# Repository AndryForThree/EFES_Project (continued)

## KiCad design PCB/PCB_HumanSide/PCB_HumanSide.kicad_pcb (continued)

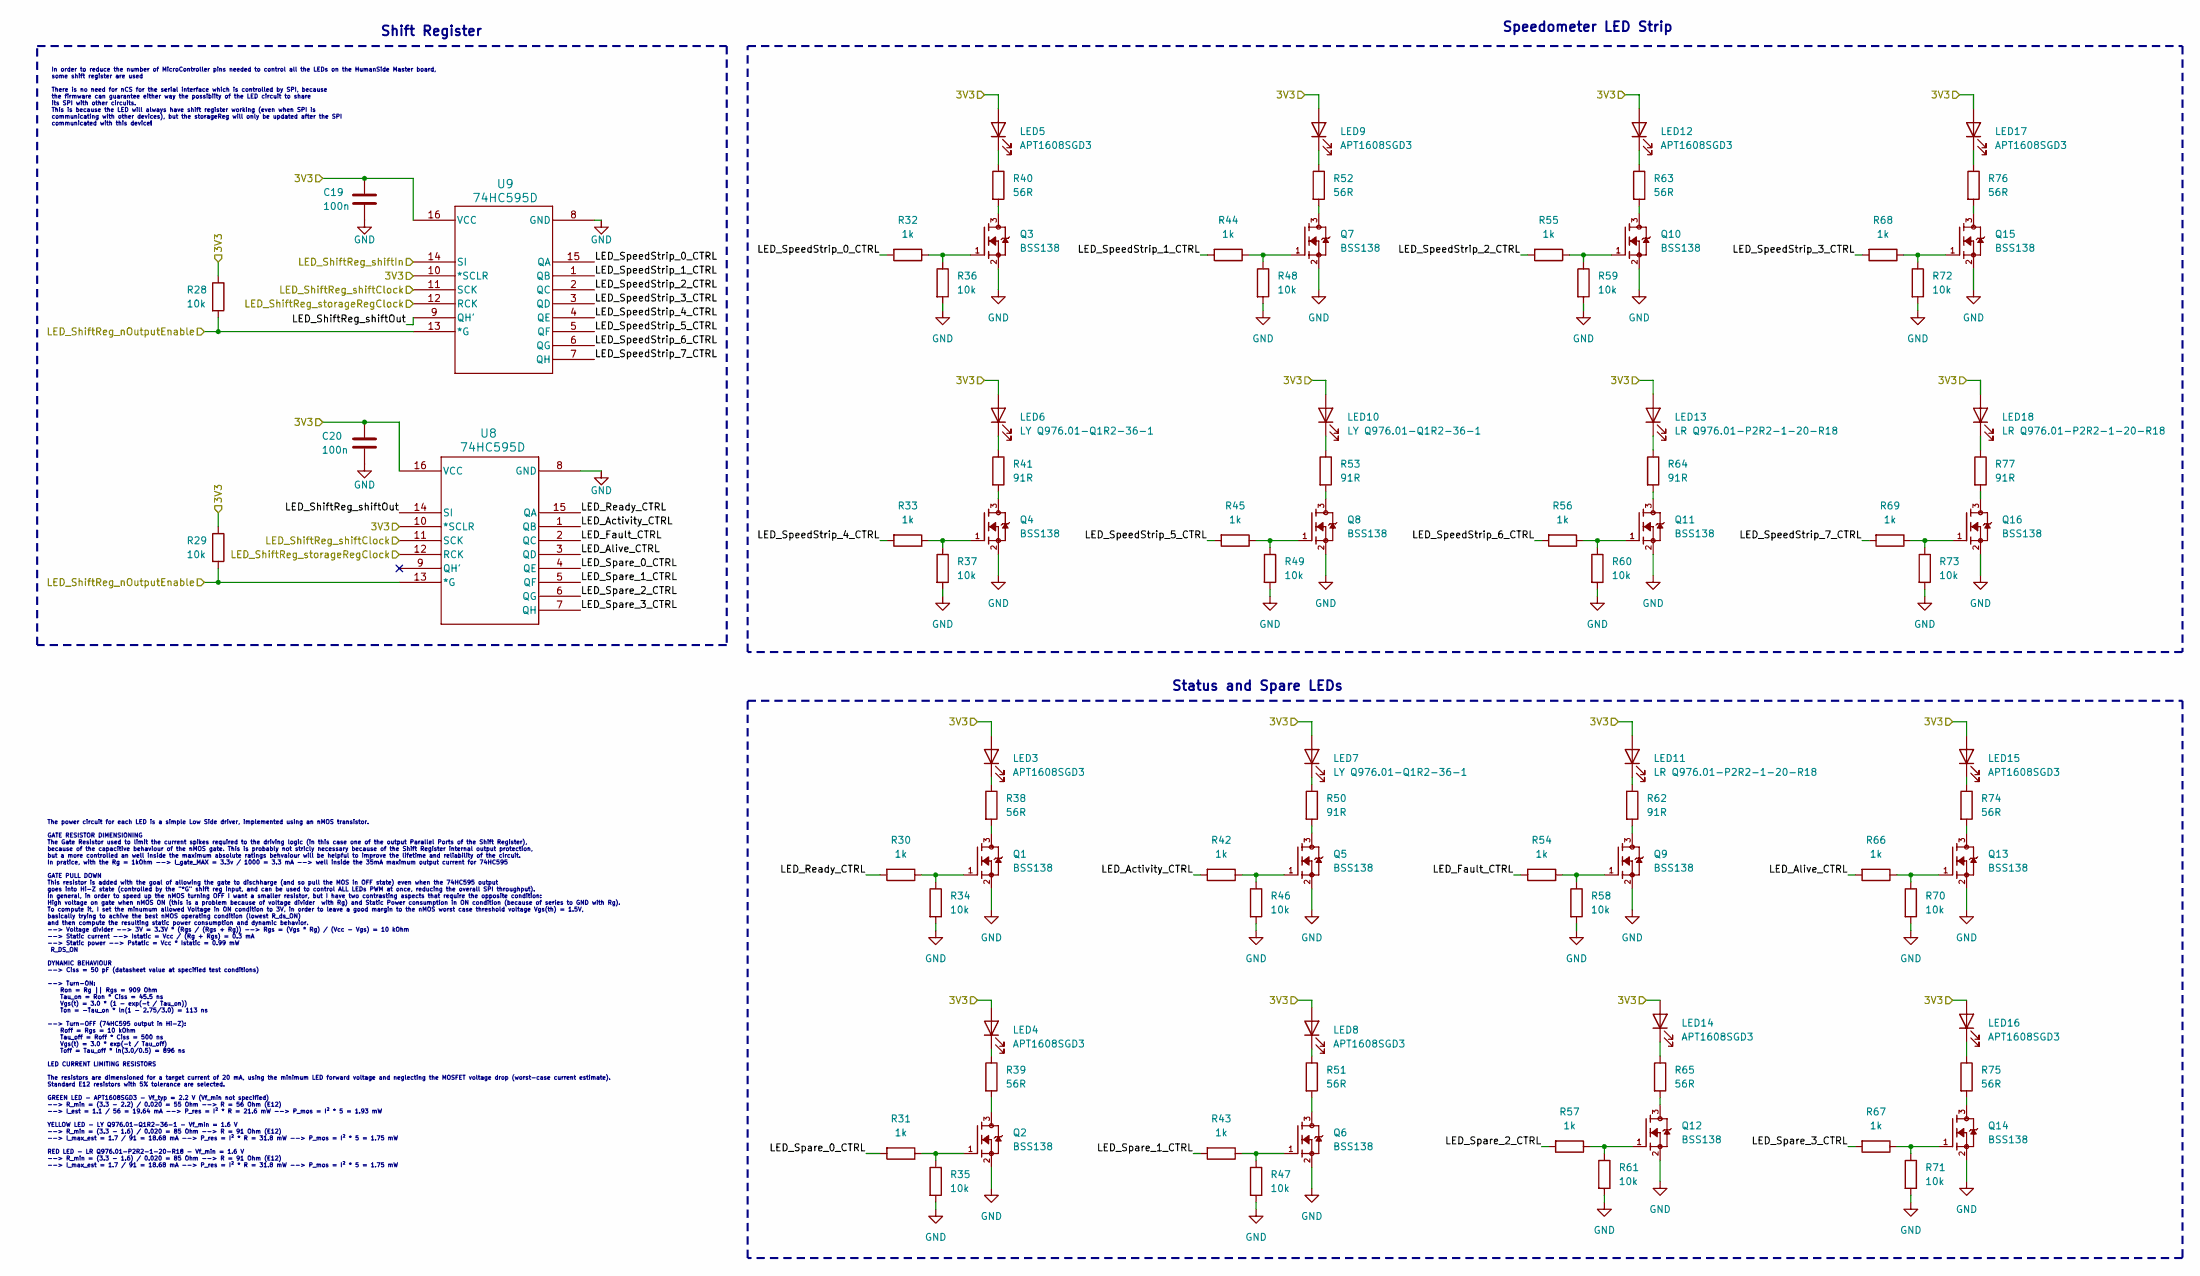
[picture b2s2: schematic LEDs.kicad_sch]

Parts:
C19, C20: 100n; C_0805_2012Metric_Pad1.18x1.45mm_HandSolder
LED3, LED4, LED5, LED8, LED9, LED12, LED14, LED15, LED16, LED17: APT1608SGD3; LED_0603_HandSolder
LED6, LED7, LED10: LY Q976.01-Q1R2-36-1; LED_0603_HandSolder
LED11, LED13, LED18: LR Q976.01-P2R2-1-20-R18; LED_0603_HandSolder
Q1, Q2, Q3, Q4, Q5, Q6, Q7, Q8, Q9, Q10, Q11, Q12, Q13, Q14, Q15, Q16: BSS138; SOT95P240X111-3N; MPN BSS138
R28, R29, R34, R35, R36, R37, R46, R47, R48, R49, R58, R59, R60, R61, R70, R71, R72, R73: 10k; R_0805_2012Metric_Pad1.20x1.40mm_HandSolder
R30, R31, R32, R33, R42, R43, R44, R45, R54, R55, R56, R57, R66, R67, R68, R69: 1k; R_0805_2012Metric_Pad1.20x1.40mm_HandSolder
R38, R39, R40, R51, R52, R63, R65, R74, R75, R76: 56R; R_0805_2012Metric_Pad1.20x1.40mm_HandSolder
R41, R50, R53, R62, R64, R77: 91R; R_0805_2012Metric_Pad1.20x1.40mm_HandSolder
U8, U9: 74HC595D; SOIC16_TOS-M

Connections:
/3V3: C19.2, C20.2, LED3.2 (A), LED4.2 (A), LED5.2 (A), LED6.2 (A), LED7.2 (A), LED8.2 (A), LED9.2 (A), LED10.2 (A), LED11.2 (A), LED12.2 (A), LED13.2 (A), LED14.2 (A), LED15.2 (A), LED16.2 (A), LED17.2 (A), LED18.2 (A), R28.1, R29.1, U8.10 (*SCLR), U8.16 (VCC), U9.10 (*SCLR), U9.16 (VCC); also elsewhere on the board
/LED_ShiftReg_nOutputEnable: R28.2, R29.2, U8.13 (*G), U9.13 (*G); also elsewhere on the board
/LED_ShiftReg_storageRegClock: U8.12 (RCK), U9.12 (RCK); also elsewhere on the board
/LEDs/LED_Activity_CTRL: R42.2, U8.1 (QB)
/LEDs/LED_Alive_CTRL: R66.2, U8.3 (QD)
/LEDs/LED_Fault_CTRL: R54.2, U8.2 (QC)
/LEDs/LED_Ready_CTRL: R30.2, U8.15 (QA)
/LEDs/LED_ShiftReg_shiftOut: U8.14 (SI), U9.9 (QH')
/LEDs/LED_Spare_0_CTRL: R31.2, U8.4 (QE)
/LEDs/LED_Spare_1_CTRL: R43.2, U8.5 (QF)
/LEDs/LED_Spare_2_CTRL: R57.2, U8.6 (QG)
/LEDs/LED_Spare_3_CTRL: R67.2, U8.7 (QH)
/LEDs/LED_SpeedStrip_0_CTRL: R32.2, U9.15 (QA)
/LEDs/LED_SpeedStrip_1_CTRL: R44.2, U9.1 (QB)
/LEDs/LED_SpeedStrip_2_CTRL: R55.2, U9.2 (QC)
/LEDs/LED_SpeedStrip_3_CTRL: R68.2, U9.3 (QD)
/LEDs/LED_SpeedStrip_4_CTRL: R33.2, U9.4 (QE)
/LEDs/LED_SpeedStrip_5_CTRL: R45.2, U9.5 (QF)
/LEDs/LED_SpeedStrip_6_CTRL: R56.2, U9.6 (QG)
/LEDs/LED_SpeedStrip_7_CTRL: R69.2, U9.7 (QH)
/PERIPH_SPI_CLK: U8.11 (SCK), U9.11 (SCK); also elsewhere on the board
/PERIPH_SPI_MOSI: U9.14 (SI); also elsewhere on the board
GND: C19.1, C20.1, Q1.2, Q2.2, Q3.2, Q4.2, Q5.2, Q6.2, Q7.2, Q8.2, Q9.2, Q10.2, Q11.2, Q12.2, Q13.2, Q14.2, Q15.2, Q16.2, R34.2, R35.2, R36.2, R37.2, R46.2, R47.2, R48.2, R49.2, R58.2, R59.2, R60.2, R61.2, R70.2, R71.2, R72.2, R73.2, U8.8 (GND), U9.8 (GND); also elsewhere on the board
unnamed: LED3.1 (K), R38.1
unnamed: LED4.1 (K), R39.1
unnamed: LED5.1 (K), R40.1
unnamed: LED6.1 (K), R41.1
unnamed: LED7.1 (K), R50.1
unnamed: LED8.1 (K), R51.1
unnamed: LED9.1 (K), R52.1
unnamed: LED10.1 (K), R53.1
unnamed: LED11.1 (K), R62.1
unnamed: LED12.1 (K), R63.1
unnamed: LED13.1 (K), R64.1
unnamed: LED14.1 (K), R65.1
unnamed: LED15.1 (K), R74.1
unnamed: LED16.1 (K), R75.1
unnamed: LED17.1 (K), R76.1
unnamed: LED18.1 (K), R77.1
unnamed: Q1.1, R30.1, R34.1
unnamed: Q1.3, R38.2
unnamed: Q2.1, R31.1, R35.1
unnamed: Q2.3, R39.2
unnamed: Q3.1, R32.1, R36.1
unnamed: Q3.3, R40.2
unnamed: Q4.1, R33.1, R37.1
unnamed: Q4.3, R41.2
unnamed: Q5.1, R42.1, R46.1
unnamed: Q5.3, R50.2
unnamed: Q6.1, R43.1, R47.1
unnamed: Q6.3, R51.2
unnamed: Q7.1, R44.1, R48.1
unnamed: Q7.3, R52.2
unnamed: Q8.1, R45.1, R49.1
unnamed: Q8.3, R53.2
unnamed: Q9.1, R54.1, R58.1
unnamed: Q9.3, R62.2
unnamed: Q10.1, R55.1, R59.1
unnamed: Q10.3, R63.2
unnamed: Q11.1, R56.1, R60.1
unnamed: Q11.3, R64.2
unnamed: Q12.1, R57.1, R61.1
unnamed: Q12.3, R65.2
unnamed: Q13.1, R66.1, R70.1
unnamed: Q13.3, R74.2
unnamed: Q14.1, R67.1, R71.1
unnamed: Q14.3, R75.2
unnamed: Q15.1, R68.1, R72.1
unnamed: Q15.3, R76.2
unnamed: Q16.1, R69.1, R73.1
unnamed: Q16.3, R77.2

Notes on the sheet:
Status and Spare LEDs
Shift Register
The power circuit for each LED is a simple Low Side driver, implemented using an nMOS transistor. GATE RESISTOR DIMENSIONING The Gate Resistor used to limit the current spikes required to the driving logic (in this case one of the output Parallel Ports of the Shift Register), because of the capacit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
In order to reduce the number of MicroController pins needed to control all the LEDs on the HumanSide Master board, some shift register are used There is no need for nCS for the serial interface which is controlled by SPI, because the firmware can guarantee either way the possibiity of the LED circ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
Speedometer LED Strip

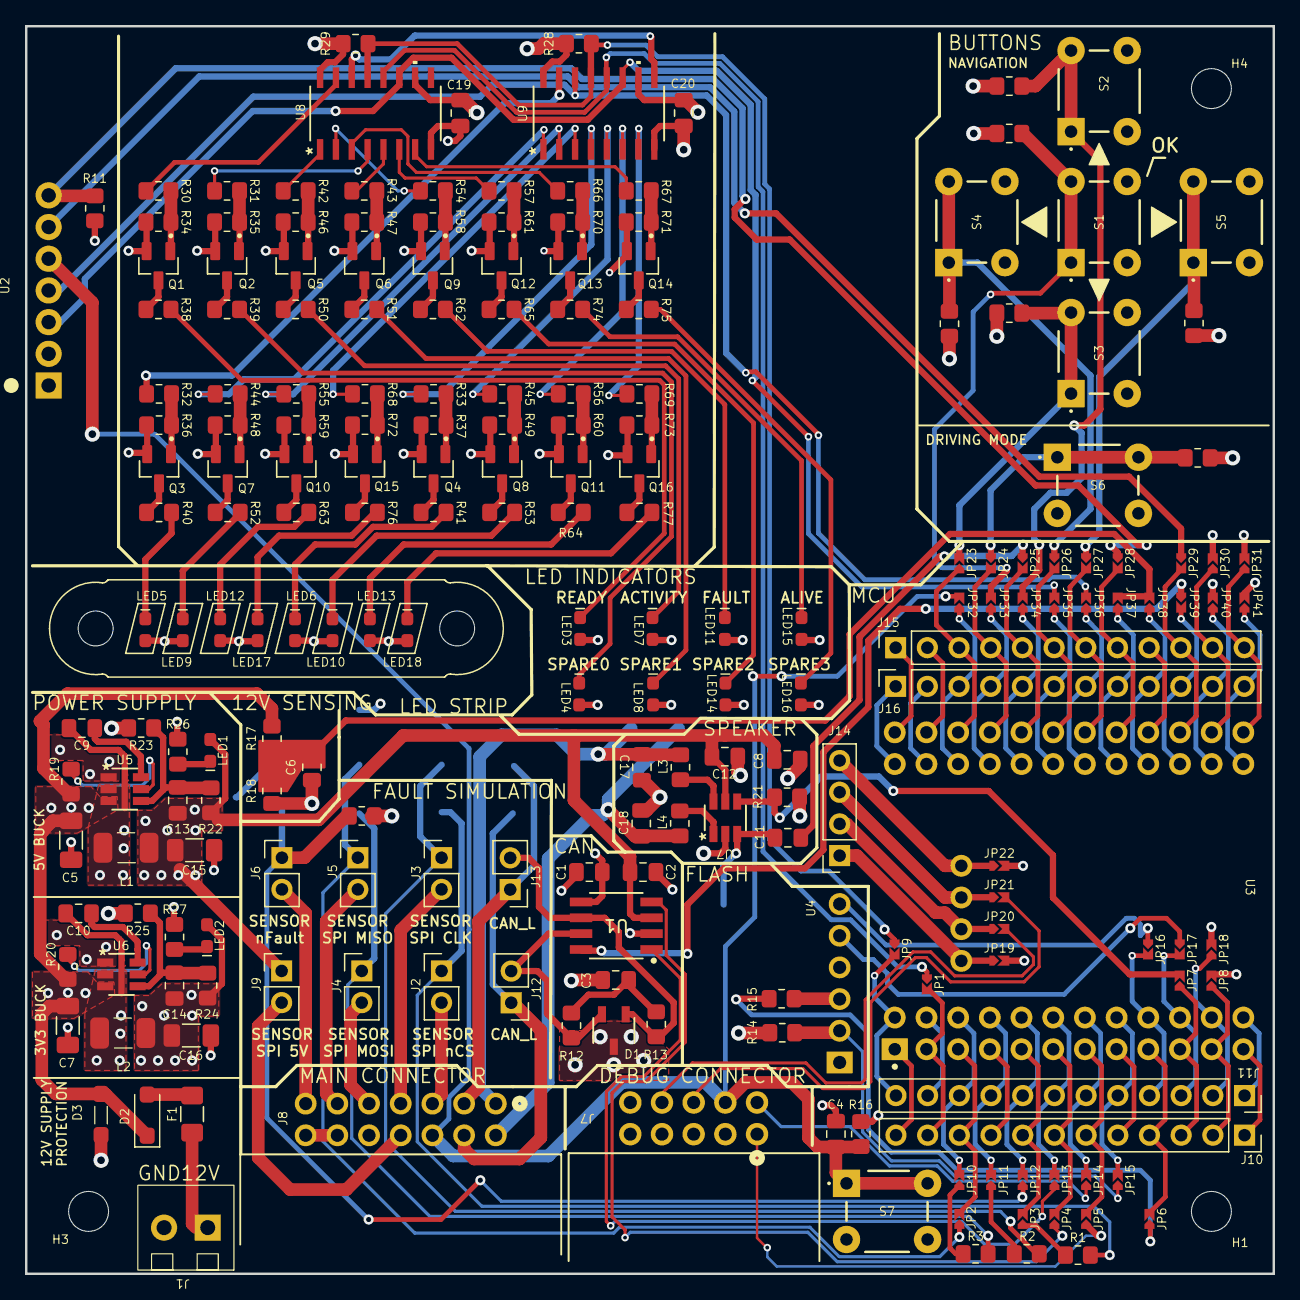
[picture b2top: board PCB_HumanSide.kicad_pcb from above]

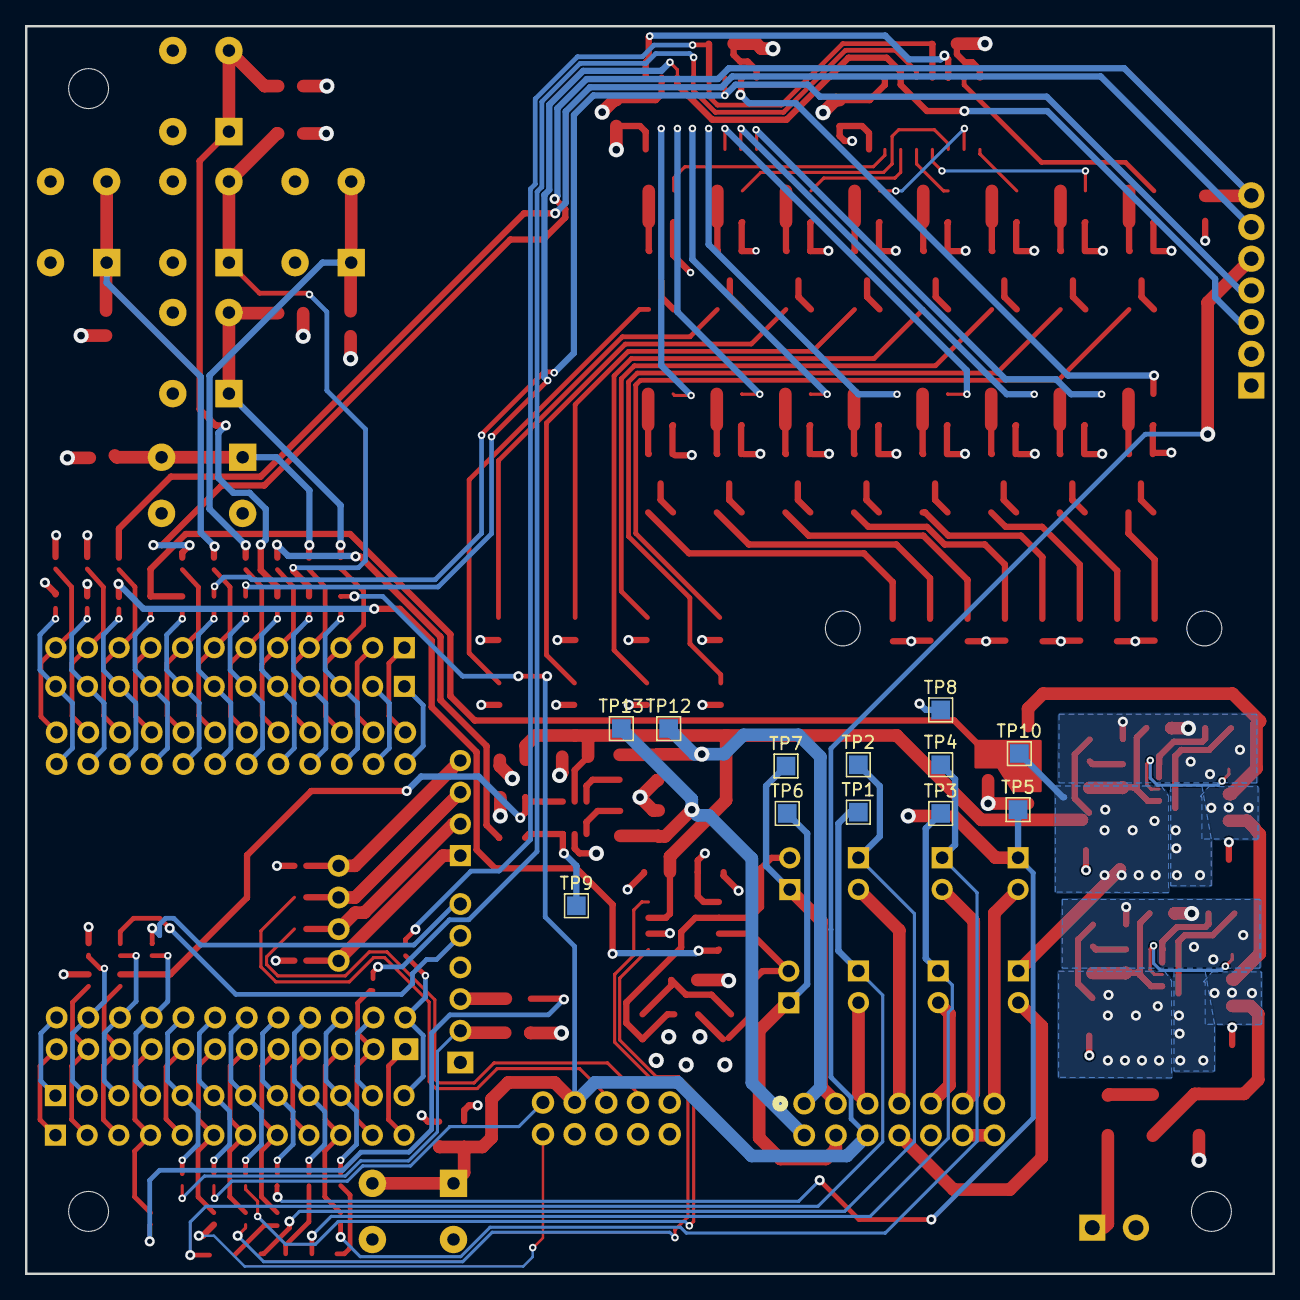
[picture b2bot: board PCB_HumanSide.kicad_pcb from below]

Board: 4 copper layers, 100.0 x 100.0 mm, 228 parts (12 on the bottom side), 186 nets.

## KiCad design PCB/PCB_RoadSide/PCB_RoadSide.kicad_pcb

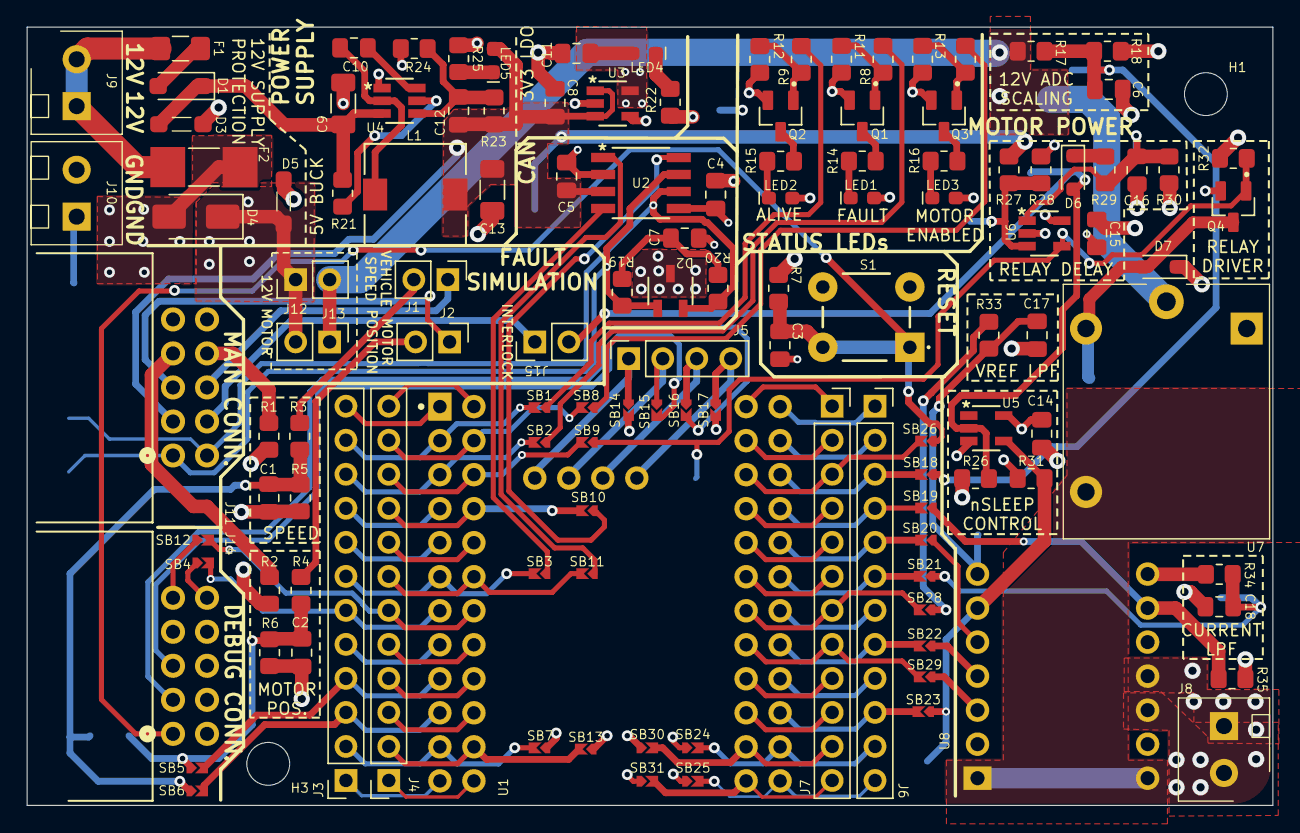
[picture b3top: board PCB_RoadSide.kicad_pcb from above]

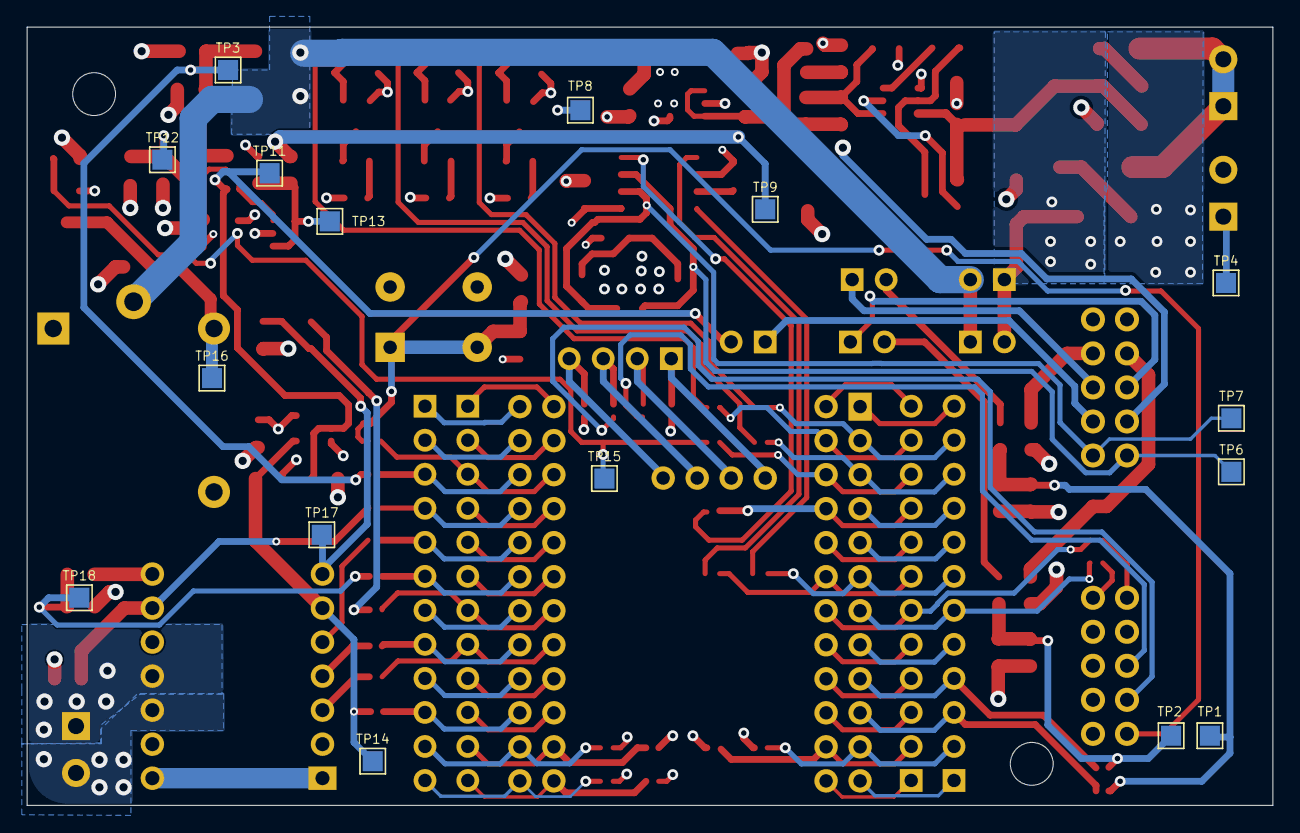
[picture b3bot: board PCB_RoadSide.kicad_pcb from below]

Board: 4 copper layers, 93.0 x 58.1 mm, 144 parts (16 on the bottom side), 118 nets.

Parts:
C1, C8, C11: 1u; C_0805_2012Metric_Pad1.18x1.45mm_HandSolder
C2: 150n; C_0805_2012Metric_Pad1.18x1.45mm_HandSolder
C3, C7, C18: 4.7n; C_0805_2012Metric_Pad1.18x1.45mm_HandSolder
C4, C5, C10, C14, C15, C17: 100n; C_0805_2012Metric_Pad1.18x1.45mm_HandSolder
C6: 1uF; C_0805_2012Metric_Pad1.18x1.45mm_HandSolder
C9: 10u; C_1206_3216Metric_Pad1.33x1.80mm_HandSolder
C12: 68p; C_0805_2012Metric_Pad1.18x1.45mm_HandSolder
C13: 47u; C_1206_3216Metric_Pad1.33x1.80mm_HandSolder
C16: 680n; C_0805_2012Metric_Pad1.18x1.45mm_HandSolder
D1: DS24W; SOD-123_HandSolder
D2: PESD2CAN24XLT-QR; SOT-23
D3, D5: SMF17CA; SOD-123_Bidirectional_HandSolder
D4: SS34; D_SMA
D6, D7: SD103AWS; D_SOD-323_HandSoldering
F1: 0.5A; Fuse_1206_3216Metric_Pad1.42x1.75mm_HandSolder
F2: 5A; FUSE_2410_HandSolder
H1, H3: MountingHole; MountingHole_3.2mm_M3
J1, J2, J12, J13, J15: Conn_01x02; PinHeader_1x02_P2.54mm_Vertical
J3, J4, J6, J7: Conn_01x12; PinSocket_1x12_P2.54mm_Vertical_TightCourtyard
J5: Conn_01x04; PinSocket_1x04_P2.54mm_Vertical
J8: Conn_01x02; CONN_TAD05-02-1-L-G
J9, J10: Conn_01x05; CONN_TAD05-02-1-L-G
J11, J14: SBH11-PBPC-D05-RA-BK; CONN_SBH11-PBPC-D05-RA-BK
L1: 27uH; INDUCT_SRR7045-270M
LED1: LR Q976.01-P2R2-1-20-R18; LED_0603_HandSolder
LED2: APT1608SGD3; LED_0603_HandSolder
LED3: LY Q976.01-Q1R2-36-1; LED_0603_HandSolder
LED4, LED5: LC191LBCT-U1; LED_0603_HandSolder
Q1, Q2, Q3, Q4: BSS138; SOT95P240X111-3N
R1, R11, R12, R13, R18, R31, R33: 10k; R_0805_2012Metric_Pad1.20x1.40mm_HandSolder
R2, R3, R8, R9, R10, R29: 1k; R_0805_2012Metric_Pad1.20x1.40mm_HandSolder
R4, R19, R20, R34: 60.4R; R_0805_2012Metric_Pad1.20x1.40mm_HandSolder
R5, R6, R23: 100k; R_0805_2012Metric_Pad1.20x1.40mm_HandSolder
R7, R26, R27, R28, R30, R32, R35: 47k; R_0805_2012Metric_Pad1.20x1.40mm_HandSolder
R14, R16: 91R; R_0805_2012Metric_Pad1.20x1.40mm_HandSolder
R15: 56R; R_0805_2012Metric_Pad1.20x1.40mm_HandSolder
R17: 84.5k; R_0805_2012Metric_Pad1.20x1.40mm_HandSolder
R21: 499k; R_0805_2012Metric_Pad1.20x1.40mm_HandSolder
R22: 82; R_0805_2012Metric_Pad1.20x1.40mm_HandSolder
R24: 13.7k; R_0805_2012Metric_Pad1.20x1.40mm_HandSolder
R25: 470; R_0805_2012Metric_Pad1.20x1.40mm_HandSolder
S1: TS02-66-50-BK-100-LCR-D; BUTTON_TS0266100BK100LCRD
SB1, SB2, SB3, SB4, SB5, SB6, SB7, SB8, SB9, SB10, SB11, SB12, SB13, SB14, SB15, SB16, SB17, SB18, SB19, SB20, SB21, SB22, SB23, SB24, SB25, SB26, SB28, SB29, SB30, SB31: SolderBride_0603
TP1, TP2, TP3, TP4, TP6, TP7, TP8, TP9, TP11, TP12, TP13, TP14, TP15, TP16, TP17, TP18: TestPoint_Probe; TestPoint_Pad_1.5x1.5mm
U1: STM32G431_WeAct
U2: ATA6563-GAQW1; SOIC8_D_TEX-M
U3: TLV70033DDCT; SOT-23-5
U4: TPS54202H; SOT-23-6_DBV_TEX-M
U5: SN74LVC1G07DBVR; SOT-23-5
U6: LMV331X-S5TR; SOT-23-5
U7: J1071AS5VDC.36; RELAY_J1071AS12VDC36
U8: H-BRIDGE_DRV8874_DevBoard

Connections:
/3V3: C4.1, C11.1, C14.2, J11.9, J11.10, J14.7, LED1.2 (A), LED2.2 (A), LED3.2 (A), LED4.2 (A), R7.2, R31.1, R32.1, R35.1, SB14.2 (B), SB25.1 (A), SB31.1 (A), TP8.1 (1_1), U2.5 (VIO), U3.5 (OUT), U5.5 (VCC)
/5V: C5.1, C8.1, C12.2, C13.2, C15.2, D7.1 (K), J11.3, L1.2, LED5.2 (A), R23.1, R27.1, TP9.1 (1_1), U2.3 (VCC), U3.1 (IN), U3.3 (EN), U6.5 (V+), U7.1
/12V: F1.1, F2.1, J9.1, J9.2
/12V_Protected_Electronics: C9.2, D1.1 (K), D3.2 (A), R21.2, U4.3 (VIN)
/12V_Protected_Motor: J12.2, J13.1, R17.2, U7.4
/ADC_12V_Motor_scaled: C6.2, R17.1, R18.2, SB18.1 (A), TP3.1 (1_1)
/ADC_MotorPosition: J2.1, J11.5
/ADC_MotorPosition_Filtered: C2.2, R4.1, R6.2, SB5.1 (A), TP2.1 (1_1)
/ADC_VehicleSpeed: J1.1, J11.6
/ADC_VehicleSpeed_Filtered: C1.2, R3.1, R5.2, SB6.1 (A), TP1.1 (1_1)
/CAN_H: D2.1 (K1), J11.1, R19.2, TP6.1 (1_1), U2.7 (CANH)
/CAN_L: D2.2 (K2), J11.2, R20.1, TP7.1 (1_1), U2.6 (CANL)
/CAN_RX: SB3.1 (A), U2.4 (RXD)
/CAN_Standby: SB10.1 (A), U2.8 (STBY)
/CAN_TX: SB11.1 (A), U2.1 (TXD)
/H-BRIDGE_PWM_VrefControl: R33.2, SB28.1 (A)
/HBRIDGE_ADC_CurrentSense: C18.2, R34.1, SB21.1 (A), TP18.1 (1_1)
/HBRIDGE_EN-IN1: SB29.1 (A), U8.3 (EN_IN1)
/HBRIDGE_PH-IN2: SB22.1 (A), U8.4 (PH_IN2)
/HBRIDGE_PMODE: SB20.1 (A), U8.5 (POE)
/HBRIDGE_nSleep: R31.2, SB23.1 (A), TP14.1 (1_1), U5.4 (Y), U8.6 (SEP)
/HBRIGE_nFAULT: R35.2, SB19.1 (A), U8.13 (FUT)
/INTERLOCK_END: J11.4, J15.1
/INTERLOCK_State: Q4.1, R32.2, SB9.1 (A), TP15.1 (1_1), U6.4 (OUT)
/LED_Alive_CTRL: R9.2, SB1.1 (A)
/LED_Fault_CTRL: R8.2, SB2.1 (A)
/LED_MotorEnable_CTRL: R10.2, SB8.1 (A)
/MOTOR_OUT+: J8.1, U8.11 (OUT1)
/MOTOR_OUT-: J8.2, U8.10 (OUT2)
/Motor_Driver/HBRIDGE_VM: U7.3, U8.1 (VM), U8.8 (VM)
/POT_MotorPosition_VSS: J11.7, R2.1
/POT_VehicleSpeed_VSS: J11.8, R1.1
/SW_CLK: J14.3, SB16.2 (B)
/SW_DIO: J14.5, SB15.2 (B)
/UART_RX: J14.9, SB12.1 (A)
/UART_TX: J14.10, SB4.1 (A)
/nRST: C3.2, J14.1, R7.1, S1.1 (NO_1), S1.2 (NO_2), SB26.1 (A)
GND: C1.1, C2.1, C3.1, C4.2, C5.2, C6.1, C7.2, C8.2, C9.1, C11.2, C13.1, C14.1, C15.1, C16.1, C17.1, C18.1, D2.3 (COM), D3.1 (K), D5.1 (K), J10.1, J10.2, J14.2, J14.6, Q1.2, Q2.2, Q3.2, Q4.2, R1.2, R2.2, R5.1, R6.1, R11.2, R12.2, R13.2, R18.1, R22.1, R24.2, R25.2, R26.1, R28.2, R30.1, S1.3 (COM_1), S1.4 (COM_2), SB7.1 (A), SB13.1 (A), SB17.2 (B), SB24.1 (A), SB30.1 (A), TP4.1 (1_1), U2.2 (GND), U3.2 (GND), U3.4 (NC), U4.1 (GND), U5.3 (GND), U6.2 (V-), U8.2 (GND), U8.9 (GND)
unnamed: C7.1, R19.1, R20.2
unnamed: D1.2 (A), F1.2
unnamed: D4.2 (A), F2.2
unnamed: D4.1 (K), D5.2 (A), J12.1, J13.2
unnamed: D6.2 (A), J15.2, R26.2, TP11.1 (1_1), U5.2 (A)
unnamed: D6.1 (K), R29.1
unnamed: D7.2 (A), Q4.3, TP16.1 (1_1), U7.2
unnamed: J1.2, R3.2
unnamed: J2.2, R4.2
unnamed: J3.1, U1.12 (VCC)
unnamed: J3.2, SB7.2 (B), U1.11 (GND)
unnamed: J3.3, SB6.2 (B), U1.10 (B12)
unnamed: J3.4, SB5.2 (B), U1.9 (B14)
unnamed: J3.5, U1.8 (C6)
unnamed: J3.6, SB4.2 (B), U1.7 (A9)
unnamed: J3.7, SB3.2 (B), U1.6 (A11)
unnamed: J3.8, U1.5 (A15)
unnamed: J3.9, U1.4 (C11)
unnamed: J3.10, SB2.2 (B), U1.3 (B4)
unnamed: J3.11, SB1.2 (B), U1.2 (B6)
unnamed: J3.12, U1.1 (B8)
unnamed: J4.1, U1.24 (VCC)
unnamed: J4.2, SB13.2 (B), U1.23 (GND)
unnamed: J4.3, U1.22 (B13)
unnamed: J4.4, U1.21 (B15)
unnamed: J4.5, U1.20 (A8)
unnamed: J4.6, SB12.2 (B), U1.19 (A10)
unnamed: J4.7, SB11.2 (B), U1.18 (A12)
unnamed: J4.8, U1.17 (C10)
unnamed: J4.9, SB10.2 (B), U1.16 (B3)
unnamed: J4.10, SB9.2 (B), U1.15 (B5)
unnamed: J4.11, SB8.2 (B), U1.14 (B7)
unnamed: J4.12, U1.13 (B9)
unnamed: J5.1, SB14.1 (A), U1.49 (3V3)
unnamed: J5.2, SB15.1 (A), U1.50 (DIO)
unnamed: J5.3, SB16.1 (A), U1.51 (CLK)
unnamed: J5.4, SB17.1 (A), U1.52 (GND)
unnamed: J6.1, U1.25 (C13)
unnamed: J6.2, U1.26 (C15)
unnamed: J6.3, SB18.2 (B), U1.27 (A0)
unnamed: J6.4, SB19.2 (B), U1.28 (A2)
unnamed: J6.5, SB20.2 (B), U1.29 (A4)
unnamed: J6.6, SB21.2 (B), U1.30 (A6)
unnamed: J6.7, U1.31 (C4)
unnamed: J6.8, SB22.2 (B), U1.32 (B1)
unnamed: J6.9, U1.33 (V+)
unnamed: J6.10, SB23.2 (B), U1.34 (B11)
unnamed: J6.11, SB24.2 (B), U1.35 (GND)
unnamed: J6.12, SB25.2 (B), U1.36 (3V3)
unnamed: J7.1, U1.37 (VB)
unnamed: J7.2, U1.38 (C14)
unnamed: J7.3, SB26.2 (B), U1.39 (NRST)
unnamed: J7.4, U1.40 (A1)
unnamed: J7.5, U1.41 (A3)
unnamed: J7.6, U1.42 (A5)
unnamed: J7.7, SB28.2 (B), U1.43 (A7)
unnamed: J7.8, SB29.2 (B), U1.44 (B0)
unnamed: J7.9, U1.45 (B2)
unnamed: J7.10, U1.46 (B10)
unnamed: J7.11, SB30.2 (B), U1.47 (GND)
unnamed: J7.12, SB31.2 (B), U1.48 (3V3)
unnamed: LED1.1 (K), R14.1
unnamed: LED2.1 (K), R15.1
unnamed: LED3.1 (K), R16.1
unnamed: LED4.1 (K), R22.2
unnamed: LED5.1 (K), R25.1
unnamed: Q1.1, R8.1, R11.1
unnamed: Q1.3, R14.2
unnamed: Q2.1, R9.1, R12.1
unnamed: Q2.3, R15.2
unnamed: Q3.1, R10.1, R13.1
unnamed: Q3.3, R16.2
unnamed: C10.1, U4.6 (BOOT)
unnamed: R21.1, U4.5 (EN)
unnamed: C12.1, R23.2, R24.1, U4.4 (FB)
unnamed: C10.2, L1.1, U4.2 (SW)
unnamed: C16.2, R29.2, R30.2, TP12.1 (1_1), U6.1 (IN+)
unnamed: R27.2, R28.1, TP13.1 (1_1), U6.3 (IN-)
unnamed: R34.2, U8.14 (CS)
unnamed: C17.2, R33.1, TP17.1 (1_1), U8.7 (VREF)

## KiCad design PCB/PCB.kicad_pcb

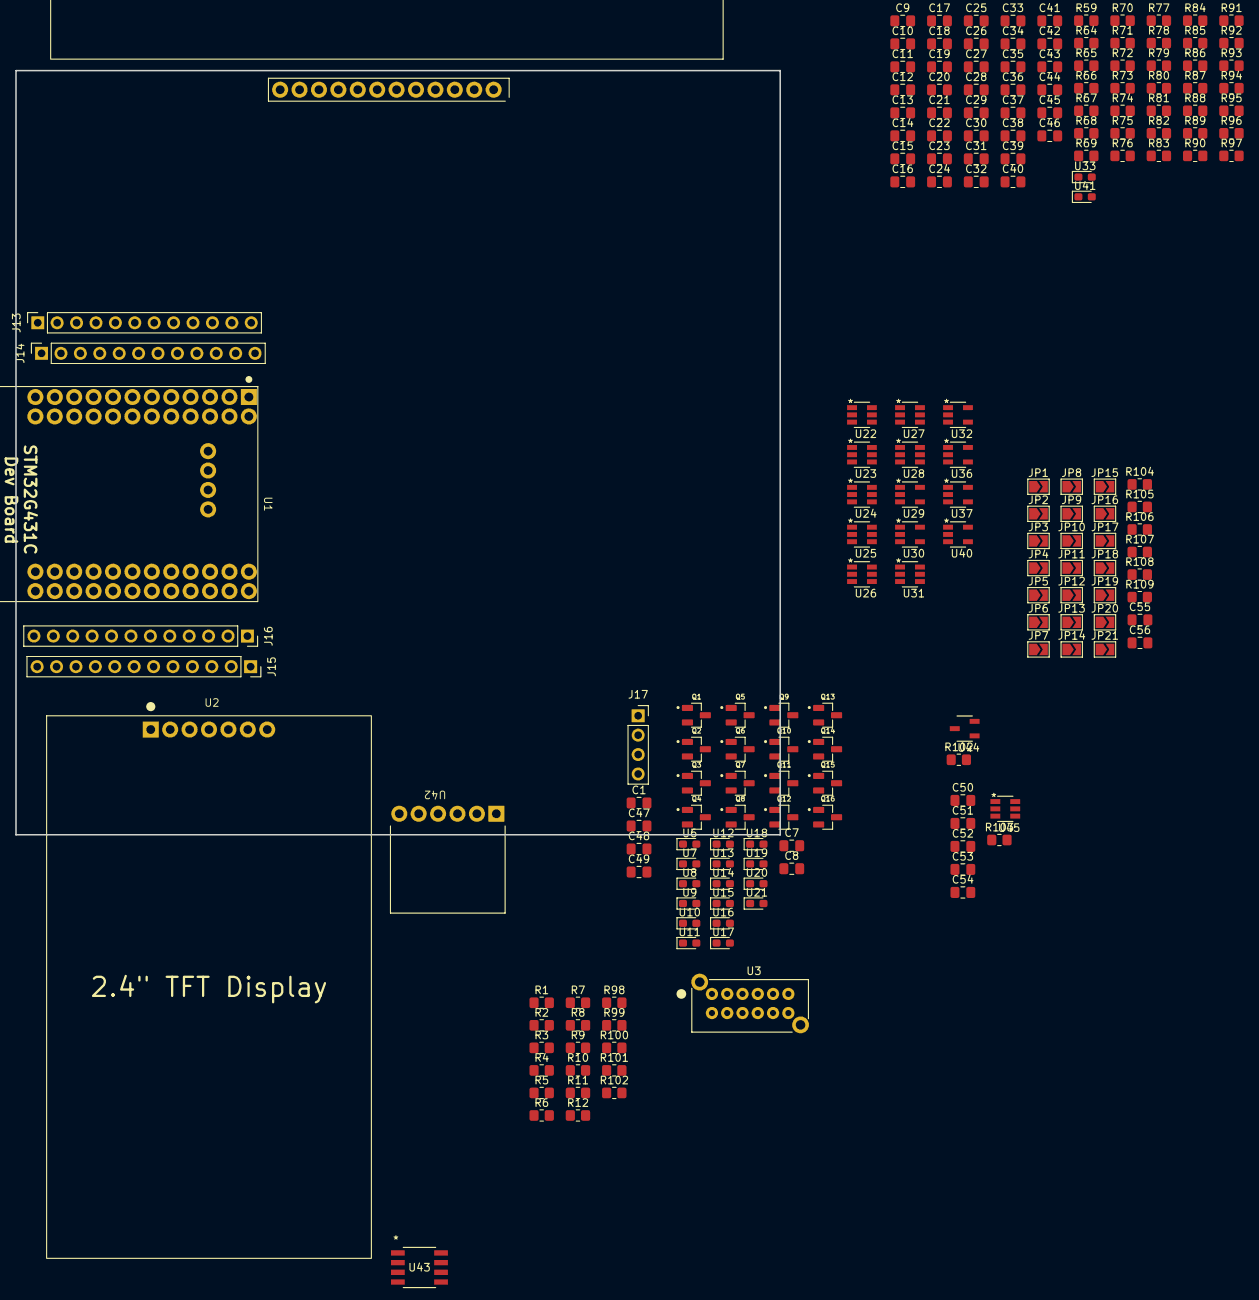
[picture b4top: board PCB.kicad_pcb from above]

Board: 2 copper layers, 100.0 x 100.0 mm, 193 parts (0 on the bottom side), 141 nets, no tracks yet.

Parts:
C1, C9, C10, C11, C12, C13, C14, C15, C16, C17, C18, C19, C20, C21, C22, C23, C24: C; C_0805_2012Metric_Pad1.18x1.45mm_HandSolder
C7, C8, C25, C26, C27, C28, C29, C30, C31, C32, C33, C34, C35, C36, C38, C39, C40, C41, C47, C48, C51, C52: 100n; C_0805_2012Metric_Pad1.18x1.45mm_HandSolder
C37, C42, C43, C44: 1u; C_0805_2012Metric_Pad1.18x1.45mm_HandSolder
C45, C46, C50: 10u; C_0805_2012Metric_Pad1.18x1.45mm_HandSolder
C49, C55: 4.7n; C_0805_2012Metric_Pad1.18x1.45mm_HandSolder
C53, C54: 220pF; C_0805_2012Metric_Pad1.18x1.45mm_HandSolder
C56: 1uF; C_0805_2012Metric_Pad1.18x1.45mm_HandSolder
J13, J14, J15, J16: Conn_01x12; PinSocket_1x12_P2.54mm_Vertical
J17: Conn_01x04; PinSocket_1x04_P2.54mm_Vertical
JP1, JP2, JP3, JP4, JP5, JP6, JP7, JP8, JP9, JP10, JP11, JP12, JP13, JP14, JP15, JP16, JP17, JP18, JP19, JP20, JP21: SolderJumper_2_Open; SolderJumper-2_P1.3mm_Open_TrianglePad1.0x1.5mm
Q1, Q2, Q3, Q4, Q5, Q6, Q7, Q8, Q9, Q10, Q11, Q12, Q13, Q14, Q15, Q16: BSS138; SOT95P240X111-3N
R1, R2, R3, R4, R5, R6, R65, R66, R69, R70, R73, R74, R77, R78, R97, R98: 0R; R_0805_2012Metric_Pad1.20x1.40mm_HandSolder
R7, R8, R9, R10, R11, R12, R79, R80, R81, R82, R90, R93, R99, R100, R103, R104, R105, R106, R107: 47k; R_0805_2012Metric_Pad1.20x1.40mm_HandSolder
R59, R64, R67, R68, R71, R72, R75, R76: R; R_0805_2012Metric_Pad1.20x1.40mm_HandSolder
R83, R94: 82; R_0805_2012Metric_Pad1.20x1.40mm_HandSolder
R84, R85, R86, R87, R95, R108: 100k; R_0805_2012Metric_Pad1.20x1.40mm_HandSolder
R88, R92: 10.5k; R_0805_2012Metric_Pad1.20x1.40mm_HandSolder
R89, R91: 68k; R_0805_2012Metric_Pad1.20x1.40mm_HandSolder
R96, R109: 10k; R_0805_2012Metric_Pad1.20x1.40mm_HandSolder
R101, R102, R102#2: 60.4R; R_0805_2012Metric_Pad1.20x1.40mm_HandSolder
U1: STM32G431_WeAct
U2: Display_GMT024-10_V2.1
U3: EG4208A; SWITCH12_EG4208A_EWI
U6, U7, U8, U9, U14, U17, U18, U19, U20, U21: APT1608SGD3; LED_0603_1608Metric_Pad1.05x0.95mm_HandSolder
U10, U11, U15: LY Q976.01-Q1R2-36-1; LED_0603_1608Metric_Pad1.05x0.95mm_HandSolder
U12, U13, U16: LR Q976.01-P2R2-1-20-R18; LED_0603_1608Metric_Pad1.05x0.95mm_HandSolder
U22, U23, U24, U25: MUX_TMUX1219DBVR; SOT-23-6_DBV_TEX-M
U26, U27: MDC97477GJ-Z; SOT-23-6_DBV_TEX-M
U28, U31: INA500BIDBVR; SOT-23-6_DBV_TEX-M
U29, U30: LMV321B-TR; SOT-23-5
U32, U40: TLV70033DDCT; SOT-23-5
U33, U41: LC191LBCT-U1; LED_0603_1608Metric_Pad1.05x0.95mm_HandSolder
U34: FPGA DevBoard; FPGA_EP4CE6E22C8N_DevBoard
U36, U37: LMV331X-S5TR; SOT-23-5
U42: FLASH_W25Q32_DevBoard
U43: ATA6563-GAQW1; SOIC8_D_TEX-M
U44: PESD2CAN24XLT-QR; SOT-23
U45: PAM8301AAF; SOT-23-6_DBV_TEX-M

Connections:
/HumanSide/5V: C48.1, C50.1, C51.1, U43.3 (VCC), U45.5 (VDD)
/HumanSide/ADC_12V_scaled: C56.2, JP18.2 (B), R108.1, R109.2
/HumanSide/CAN_H: R101.2, U43.7 (CANH), U44.1 (K1)
/HumanSide/CAN_L: R102#2.1, U43.6 (CANL), U44.2 (K2)
/HumanSide/CAN_RX: JP2.1 (A), U43.4 (RXD)
/HumanSide/CAN_TX: JP5.1 (A), U43.1 (TXD)
/HumanSide/DOWN_Button: R3.2, R8.2
/HumanSide/FLASH_SPI_CLK: JP8.1 (A), U42.5 (CLK)
/HumanSide/FLASH_SPI_MISO: JP4.1 (A), R98.1
/HumanSide/FLASH_SPI_MOSI: JP7.1 (A), U42.6 (DI)
/HumanSide/FLASH_SPI_nCS: R99.1, U42.2 (CS)
/HumanSide/LEFT_Button: R5.2, R10.2
/HumanSide/MODE_Button: R6.2, R11.2
/HumanSide/OK_Button: C1.1, R1.2, R12.2
/HumanSide/PERIPH_SPI_nCS_DISPLAY: R100.1, U2.7 (CS)
/HumanSide/RIGHT_Button: R4.2, R9.2
/HumanSide/SPEAKER_AnalogIn: C52.1, JP9.2 (B)
/HumanSide/SPEAKER_nShutdown: R103.2, U45.4 (nSD)
/HumanSide/UP_Button: R2.2, R7.2
/HumanSide/nRST: C55.2, JP1.2 (B), R107.1, U2.5 (RST)
/SWCLK_HumanSide: JP21.2 (B), U3.7
/SWDIO_HumanSide: JP20.2 (B), U3.1
/SensorPCB/3V3_Analog_CH1: C25.1, C26.1, C29.1, C31.1, C32.1, C38.1, C40.1, C45.1, R79.2, R84.2, R89.2, R95.2, U22.2 (VDD), U23.2 (VDD), U26.1 (Vdd), U28.6 (V+), U29.5 (V+), U33.2 (A), U36.5 (V+)
/SensorPCB/3V3_Analog_CH2: C27.1, C28.1, C30.1, C35.1, C36.1, C39.1, C41.1, C43.1, C46.1, R81.2, R85.2, R91.2, U24.2 (VDD), U25.2 (VDD), U27.1 (Vdd), U30.5 (V+), U31.6 (V+), U37.5 (V+), U40.5 (OUT), U41.2 (A)
/SensorPCB/3V3_Digital: R90.2, R93.2
/SensorPCB/CH1_ADC_CLK: U26.4 (SCLK), U34.2 (PIN_6)
/SensorPCB/CH1_ADC_CS: R84.1, U26.6 (CS), U34.1 (PIN_5)
/SensorPCB/CH1_ADC_IN: U26.3 (Vin), U28.4 (OUT)
/SensorPCB/CH1_COS+_FILTERED: C14.1, C15.2, R69.2, U23.6 (S2)
/SensorPCB/CH1_COS-_FILTERED: C14.2, C16.1, R70.2, U22.6 (S2)
/SensorPCB/CH1_MUX+_OUTPUT: U23.5 (D), U28.1 (IN+)
/SensorPCB/CH1_MUX-_OUTPUT: U22.5 (D), U28.3 (IN-)
/SensorPCB/CH1_MUX_SELECTOR: R86.2, U22.1 (SEL), U23.1 (SEL), U34.4 (PIN_8)
/SensorPCB/CH1_SIN-_FILTERED: C10.2, C12.1, R66.2, U22.4 (S1)
/SensorPCB/CH1_VDIAG_GPIO: R90.1, U34.5 (PIN_9), U36.4 (OUT)
/SensorPCB/CH2_ADC_CLK: U27.4 (SCLK), U34.7 (PIN_11)
/SensorPCB/CH2_ADC_CS: R85.1, U27.6 (CS), U34.6 (PIN_10)
/SensorPCB/CH2_ADC_IN: U27.3 (Vin), U31.4 (OUT)
/SensorPCB/CH2_ADC_MISO: U27.5 (SDATA), U34.8 (PIN_12)
/SensorPCB/CH2_COS+_FILTERED: C22.1, C23.2, R77.2, U25.6 (S2)
/SensorPCB/CH2_COS-_FILTERED: C22.2, C24.1, R78.2, U24.6 (S2)
/SensorPCB/CH2_MUX+_OUTPUT: U25.5 (D), U31.1 (IN+)
/SensorPCB/CH2_MUX-_OUTPUT: U24.5 (D), U31.3 (IN-)
/SensorPCB/CH2_MUX_SELECTOR: R87.2, U24.1 (SEL), U25.1 (SEL), U34.9 (PIN_13)
/SensorPCB/CH2_SIN+_FILTERED: C18.1, C19.2, R73.2, U25.4 (S1)
/SensorPCB/CH2_SIN-_FILTERED: C18.2, C20.1, R74.2, U24.4 (S1)
/SensorPCB/CH2_VDIAG_GPIO: R93.1, U34.10 (PIN_14), U37.4 (OUT)
/VTRef_HumanSide: C7.2, C8.2, C47.1, JP14.2 (B), JP15.2 (B), JP16.2 (B), JP17.2 (B), JP19.2 (B), R99.2, R100.2, R107.2, U3.10, U42.1 (VCC), U43.5 (VIO)
GND: C1.2, C7.1, C8.1, C11.1, C12.2, C15.1, C16.2, C19.1, C20.2, C23.1, C24.2, C25.2, C26.2, C27.2, C28.2, C29.2, C30.2, C31.2, C32.2, C33.2, C34.2, C35.2, C36.2, C37.2, C38.2, C39.2, C40.2, C41.2, C42.2, C43.2, C44.2, C45.2, C46.2, C47.2, C48.2, C49.2, C50.2, C51.2, C53.2, C54.2, C55.1, C56.1, JP10.2 (B), JP11.2 (B), JP12.2 (B), JP13.2 (B), Q1.2, Q2.2, Q3.2, Q4.2, Q5.2, Q6.2, Q7.2, Q8.2, Q9.2, Q10.2, Q11.2, Q12.2, Q13.2, Q14.2, Q15.2, Q16.2, R7.1, R8.1, R9.1, R10.1, R11.1, R12.1, R80.1, R82.1, R83.1, R86.1, R87.1, R88.1, R92.1, R94.1, R96.1, R103.1, R109.1, U2.1 (GND), U22.3 (GND), U23.3 (GND), U24.3 (GND), U25.3 (GND), U26.2 (GND), U27.2 (GND), U28.2 (V-), U29.2 (V-), U30.2 (V-), U31.2 (V-), U32.2 (GND), U32.4 (NC), U36.2 (V-), U37.2 (V-), U40.2 (GND), U40.4 (NC), U42.4 (GND), U43.2 (GND), U44.3 (COM), U45.2 (GND)
unnamed: C9.1, R59.2, R65.1
unnamed: C9.2, R64.2, R66.1
unnamed: C13.1, R67.2, R69.1
unnamed: C13.2, R68.2, R70.1
unnamed: C17.1, R71.2, R73.1
unnamed: C17.2, R72.2, R74.1
unnamed: C21.1, R75.2, R77.1
unnamed: C21.2, R76.2, R78.1
unnamed: C49.1, R101.1, R102.2, R102#2.2
unnamed: C10.1, C11.2, R65.2
unnamed: R95.1, R96.2
unnamed: C44.1, U32.5 (OUT)
unnamed: J13.1, JP14.1 (A), U1.12 (VCC)
unnamed: J13.2, JP13.1 (A), U1.11 (GND)
unnamed: J13.3, U1.10 (B12)
unnamed: J13.4, JP4.2 (B), U1.9 (B14)
unnamed: J13.5, U1.8 (C6)
unnamed: J13.6, JP3.2 (B), U1.7 (A9)
unnamed: J13.7, JP2.2 (B), U1.6 (A11)
unnamed: J13.8, U1.5 (A15)
unnamed: J13.9, U1.4 (C11)
unnamed: J13.10, U1.3 (B4)
unnamed: J13.11, U1.2 (B6)
unnamed: J13.12, U1.1 (B8)
unnamed: J14.1, JP15.1 (A), U1.24 (VCC)
unnamed: J14.2, JP12.1 (A), U1.23 (GND)
unnamed: J14.3, JP8.2 (B), U1.22 (B13)
unnamed: J14.4, JP7.2 (B), U1.21 (B15)
unnamed: J14.5, U1.20 (A8)
unnamed: J14.6, JP6.2 (B), U1.19 (A10)
unnamed: J14.7, JP5.2 (B), U1.18 (A12)
unnamed: J14.8, U1.17 (C10)
unnamed: J14.9, U1.16 (B3)
unnamed: J14.10, U1.15 (B5)
unnamed: J14.11, U1.14 (B7)
unnamed: J14.12, U1.13 (B9)
unnamed: J15.1, U1.37 (VB)
unnamed: J15.2, U1.38 (C14)
unnamed: J15.3, JP1.1 (A), U1.39 (NRST)
unnamed: J15.4, U1.40 (A1)
unnamed: J15.5, U1.41 (A3)
unnamed: J15.6, JP9.1 (A), U1.42 (A5)
unnamed: J15.7, U1.43 (A7)
unnamed: J15.8, U1.44 (B0)
unnamed: J15.9, U1.45 (B2)
unnamed: J15.10, U1.46 (B10)
unnamed: J15.11, JP11.1 (A), U1.47 (GND)
unnamed: J15.12, JP16.1 (A), U1.48 (3V3)
unnamed: J16.1, U1.25 (C13)
unnamed: J16.2, U1.26 (C15)
unnamed: J16.3, JP18.1 (A), U1.27 (A0)
unnamed: J16.4, U1.28 (A2)
unnamed: J16.5, U1.29 (A4)
unnamed: J16.6, U1.30 (A6)
unnamed: J16.7, U1.31 (C4)
unnamed: J16.8, U1.32 (B1)
unnamed: J16.9, U1.33 (V+)
unnamed: J16.10, U1.34 (B11)
unnamed: J16.11, JP10.1 (A), U1.35 (GND)
unnamed: J16.12, JP17.1 (A), U1.36 (3V3)
unnamed: J17.1, JP19.1 (A), U1.49 (3V3)
unnamed: J17.2, JP20.1 (A), U1.50 (DIO)
unnamed: J17.3, JP21.1 (A), U1.51 (CLK)
unnamed: J17.4, U1.52 (GND)
unnamed: Q1.3, U6.1 (K)
unnamed: Q2.3, U7.1 (K)
unnamed: Q5.3, U8.1 (K)
unnamed: Q7.3, U9.1 (K)
unnamed: Q3.3, U10.1 (K)
unnamed: Q4.3, U11.1 (K)
unnamed: Q6.3, U12.1 (K)
unnamed: Q8.3, U13.1 (K)
unnamed: Q9.3, U14.1 (K)
unnamed: Q12.3, U15.1 (K)
unnamed: Q15.3, U16.1 (K)
unnamed: Q10.3, U17.1 (K)
unnamed: Q14.3, U18.1 (K)
unnamed: Q11.3, U19.1 (K)
unnamed: Q16.3, U20.1 (K)
unnamed: Q13.3, U21.1 (K)
unnamed: U28.5 (REF), U29.3 (IN-), U29.4 (OUT)
unnamed: C33.1, R79.1, R80.2, U29.1 (IN+)
unnamed: C34.1, R81.1, R82.2, U30.1 (IN+)
unnamed: U30.3 (IN-), U30.4 (OUT), U31.5 (REF)
unnamed: C37.1, U32.1 (IN), U32.3 (EN)
unnamed: R83.2, U33.1 (K)
unnamed: R88.2, R89.1, U36.3 (IN-)
unnamed: R91.1, R92.2, U37.3 (IN-)
unnamed: C42.1, U40.1 (IN), U40.3 (EN)
unnamed: R94.2, U41.1 (K)
unnamed: R98.2, U42.3 (DO)
unnamed: C52.2, U45.3 (IN)
